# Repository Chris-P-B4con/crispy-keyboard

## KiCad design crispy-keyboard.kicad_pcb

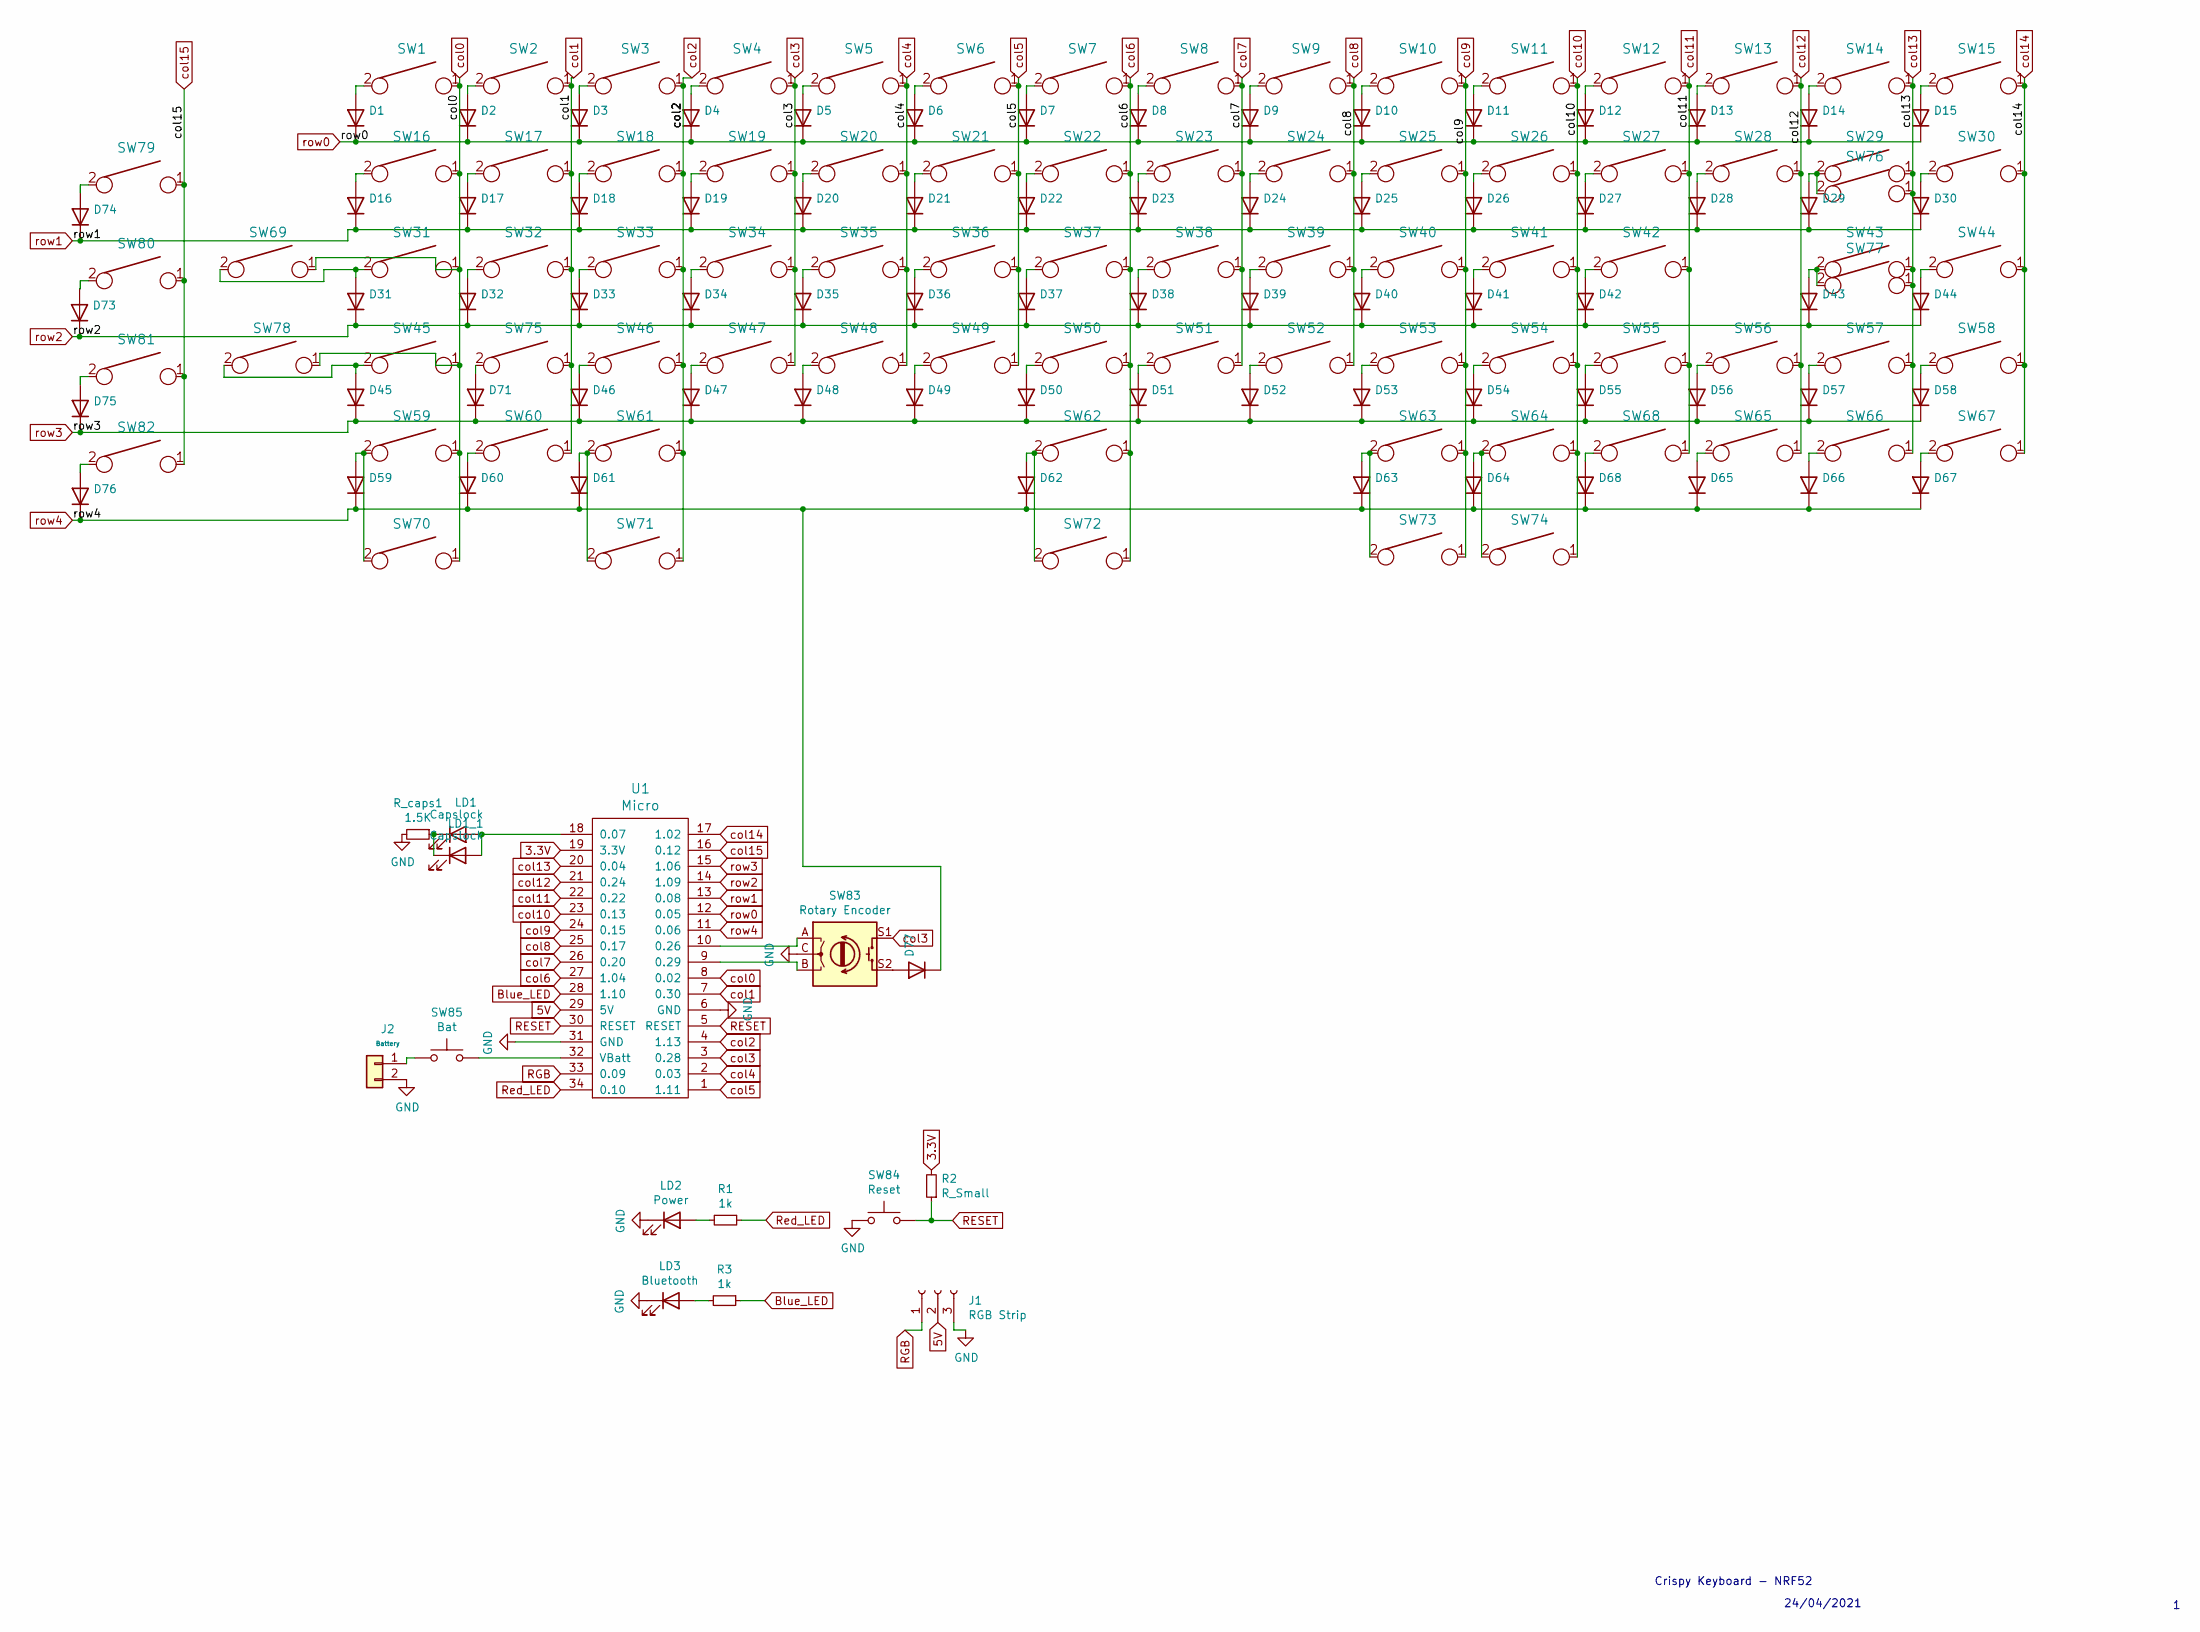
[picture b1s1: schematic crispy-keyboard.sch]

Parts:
D1, D2, D3, D4, D5, D6, D7, D8, D9, D10, D11, D12, D13, D14, D15, D16, D17, D18, D19, D20, D21, D22, D23, D24, D25, D26, D27, D28, D29, D30, D31, D32, D33, D34, D35, D36, D37, D38, D39, D40, D41, D42, D43, D44, D45, D46, D47, D48, D49, D50, D51, D52, D53, D54, D55, D56, D57, D58, D59, D60, D61, D62, D63, D64, D65, D66, D67, D68, D71, D73, D74, D75, D76, D77: D_DO-35_SOD27_P5.08mm_Horizontal
J1: RGB Strip; PinHeader_1x03_P2.00mm_Horizontal
J2: Battery; PinHeader_1x02_P2.54mm_Vertical
LD1, LD1_1: Capslock; LED_D3.0mm
LD2: Power; LED_D3.0mm
LD3: Bluetooth; LED_D3.0mm
R1, R3: 1k; R_Axial_DIN0204_L3.6mm_D1.6mm_P5.08mm_Horizontal
R2: R_Small; R_Axial_DIN0204_L3.6mm_D1.6mm_P5.08mm_Horizontal
R_caps1: 1.5K; R_Axial_DIN0204_L3.6mm_D1.6mm_P5.08mm_Horizontal
SW1, SW2, SW3, SW4, SW5, SW6, SW7, SW8, SW9, SW10, SW11, SW12, SW13, SW15, SW17, SW18, SW19, SW20, SW21, SW22, SW23, SW24, SW25, SW26, SW27, SW28, SW30, SW32, SW33, SW34, SW35, SW36, SW37, SW38, SW39, SW40, SW41, SW42, SW44, SW46, SW47, SW48, SW49, SW50, SW51, SW52, SW53, SW54, SW55, SW57, SW58, SW62, SW65, SW66, SW67, SW68, SW72, SW75, SW77, SW79, SW80, SW81, SW82: KEYSW; SW_Cherry_MX1A_1.00u_PCB-NOSCREEN
SW14: KEYSW; SW_Cherry_MX1A_2.00u_PCBNOSCREEN
SW16, SW29, SW70, SW71, SW73, SW74: KEYSW; SW_Cherry_MX1A_1.50u_PCBNOSCREEN
SW31, SW56: KEYSW; SW_Cherry_MX1A_1.75u_PCBNOSCREEN
SW43, SW45: KEYSW; SW_Cherry_MX1A_2.25u_PCBNOSCREEN
SW59, SW60, SW61, SW63, SW64, SW69, SW78: KEYSW; SW_Cherry_MX1A_1.25u_PCBNOSCREEN
SW76: KEYSW; SW_Cherry_MX1A_ISOEnter_PCB_ReversedStabilizer
SW83: Rotary Encoder; Bourns-PEC11R-4120F-S0018-MFG
SW84: Reset; SW_PUSH_6mm
SW85: Bat; CK_Switches-L101011ML04Q-0-0-MFG
U1: Micro; arduino_micro_large

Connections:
3.3V: R2.2, U1.19 (3.3V)
5V: J1.2, U1.29 (5V)
Blue_LED: R3.1, U1.28 (1.10)
GND: J1.3, J2.2, LD2.1 (K), LD3.1 (K), R_caps1.2, SW83.C, SW84.2, U1.6 (GND), U1.31 (GND); also elsewhere on the board
unnamed: D1.2 (A), SW1.2
unnamed: D2.2 (A), SW2.2
unnamed: D3.2 (A), SW3.2
unnamed: D4.2 (A), SW4.2
unnamed: D5.2 (A), SW5.2
unnamed: D6.2 (A), SW6.2
unnamed: D7.2 (A), SW7.2
unnamed: D8.2 (A), SW8.2
unnamed: D9.2 (A), SW9.2
unnamed: D10.2 (A), SW10.2
unnamed: D11.2 (A), SW11.2
unnamed: D12.2 (A), SW12.2
unnamed: D13.2 (A), SW13.2
unnamed: D14.2 (A), SW14.2
unnamed: D15.2 (A), SW15.2
unnamed: D16.2 (A), SW16.2
unnamed: D17.2 (A), SW17.2
unnamed: D18.2 (A), SW18.2
unnamed: D19.2 (A), SW19.2
unnamed: D20.2 (A), SW20.2
unnamed: D21.2 (A), SW21.2
unnamed: D22.2 (A), SW22.2
unnamed: D23.2 (A), SW23.2
unnamed: D24.2 (A), SW24.2
unnamed: D25.2 (A), SW25.2
unnamed: D26.2 (A), SW26.2
unnamed: D27.2 (A), SW27.2
unnamed: D28.2 (A), SW28.2
unnamed: D29.2 (A), SW29.2, SW76.2
unnamed: D30.2 (A), SW30.2
unnamed: D31.2 (A), SW31.2, SW69.2
unnamed: D32.2 (A), SW32.2
unnamed: D33.2 (A), SW33.2
unnamed: D34.2 (A), SW34.2
unnamed: D35.2 (A), SW35.2
unnamed: D36.2 (A), SW36.2
unnamed: D37.2 (A), SW37.2
unnamed: D38.2 (A), SW38.2
unnamed: D39.2 (A), SW39.2
unnamed: D40.2 (A), SW40.2
unnamed: D41.2 (A), SW41.2
unnamed: D42.2 (A), SW42.2
unnamed: D43.2 (A), SW43.2, SW77.2
unnamed: D44.2 (A), SW44.2
unnamed: D45.2 (A), SW45.2, SW78.2
unnamed: D46.2 (A), SW46.2
unnamed: D47.2 (A), SW47.2
unnamed: D48.2 (A), SW48.2
unnamed: D49.2 (A), SW49.2
unnamed: D50.2 (A), SW50.2
unnamed: D51.2 (A), SW51.2
unnamed: D52.2 (A), SW52.2
unnamed: D53.2 (A), SW53.2
unnamed: D54.2 (A), SW54.2
unnamed: D55.2 (A), SW55.2
unnamed: D56.2 (A), SW56.2
unnamed: D57.2 (A), SW57.2
unnamed: D58.2 (A), SW58.2
unnamed: D59.2 (A), SW59.2, SW70.2
unnamed: D60.2 (A), SW60.2
unnamed: D61.2 (A), SW61.2, SW71.2
unnamed: D62.2 (A), SW62.2, SW72.2
unnamed: D63.2 (A), SW63.2, SW73.2
unnamed: D64.2 (A), SW64.2, SW74.2
unnamed: D65.2 (A), SW65.2
unnamed: D66.2 (A), SW66.2
unnamed: D67.2 (A), SW67.2
unnamed: D68.2 (A), SW68.2
unnamed: D71.2 (A), SW75.2
unnamed: D73.2 (A), SW80.2
unnamed: D74.2 (A), SW79.2
unnamed: D75.2 (A), SW81.2
unnamed: D76.2 (A), SW82.2
unnamed: D77.2 (A), SW83.S2
unnamed: J2.1, SW85.2
unnamed: LD1.1 (K), LD1_1.1 (K), R_caps1.1
unnamed: LD1.2 (A), LD1_1.2 (A), U1.18 (0.07)
unnamed 81: LD2.2 (A), R1.2; also elsewhere on the board
unnamed 82: LD3.2 (A), R3.2; also elsewhere on the board
unnamed: SW83.A, U1.10 (0.26)
unnamed: SW83.B, U1.9 (0.29)
unnamed: SW85.1, U1.32 (VBatt)
RESET: R2.1, SW84.1, U1.5 (RESET), U1.30 (RESET)
RGB: J1.1, U1.33 (0.09)
Red_LED: R1.1, U1.34 (0.10)
col0: SW1.1, SW16.1, SW31.1, SW45.1, SW59.1, SW69.1, SW70.1, SW78.1, U1.8 (0.02)
col1: SW2.1, SW17.1, SW32.1, SW60.1, SW75.1, U1.7 (0.30)
col2: SW3.1, SW18.1, SW33.1, SW46.1, SW61.1, SW71.1, U1.4 (1.13)
col3: SW4.1, SW19.1, SW34.1, SW47.1, SW83.S1, U1.3 (0.28)
col4: SW5.1, SW20.1, SW35.1, SW48.1, U1.2 (0.03)
col5: SW6.1, SW21.1, SW36.1, SW49.1, U1.1 (1.11)
col6: SW7.1, SW22.1, SW37.1, SW50.1, SW62.1, SW72.1, U1.27 (1.04)
col7: SW8.1, SW23.1, SW38.1, SW51.1, U1.26 (0.20)
col8: SW9.1, SW24.1, SW39.1, SW52.1, U1.25 (0.17)
col9: SW10.1, SW25.1, SW40.1, SW53.1, SW63.1, SW73.1, U1.24 (0.15)
col10: SW11.1, SW26.1, SW41.1, SW54.1, SW64.1, SW74.1, U1.23 (0.13)
col11: SW12.1, SW27.1, SW42.1, SW55.1, SW68.1, U1.22 (0.22)
col12: SW13.1, SW28.1, SW56.1, SW65.1, U1.21 (0.24)
col13: SW14.1, SW29.1, SW43.1, SW57.1, SW66.1, SW76.1, SW77.1, U1.20 (0.04)
col14: SW15.1, SW30.1, SW44.1, SW58.1, SW67.1, U1.17 (1.02)
col15: SW79.1, SW80.1, SW81.1, SW82.1, U1.16 (0.12)
row0: D1.1 (K), D2.1 (K), D3.1 (K), D4.1 (K), D5.1 (K), D6.1 (K), D7.1 (K), D8.1 (K), D9.1 (K), D10.1 (K), D11.1 (K), D12.1 (K), D13.1 (K), D14.1 (K), D15.1 (K), U1.12 (0.05)
row1: D16.1 (K), D17.1 (K), D18.1 (K), D19.1 (K), D20.1 (K), D21.1 (K), D22.1 (K), D23.1 (K), D24.1 (K), D25.1 (K), D26.1 (K), D27.1 (K), D28.1 (K), D29.1 (K), D30.1 (K), D74.1 (K), U1.13 (0.08)
row2: D31.1 (K), D32.1 (K), D33.1 (K), D34.1 (K), D35.1 (K), D36.1 (K), D37.1 (K), D38.1 (K), D39.1 (K), D40.1 (K), D41.1 (K), D42.1 (K), D43.1 (K), D44.1 (K), D73.1 (K), U1.14 (1.09)
row3: D45.1 (K), D46.1 (K), D47.1 (K), D48.1 (K), D49.1 (K), D50.1 (K), D51.1 (K), D52.1 (K), D53.1 (K), D54.1 (K), D55.1 (K), D56.1 (K), D57.1 (K), D58.1 (K), D71.1 (K), D75.1 (K), U1.15 (1.06)
row4: D59.1 (K), D60.1 (K), D61.1 (K), D62.1 (K), D63.1 (K), D64.1 (K), D65.1 (K), D66.1 (K), D67.1 (K), D68.1 (K), D76.1 (K), D77.1 (K), U1.11 (0.06)

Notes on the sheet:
24/04/2021
Crispy Keyboard - NRF52

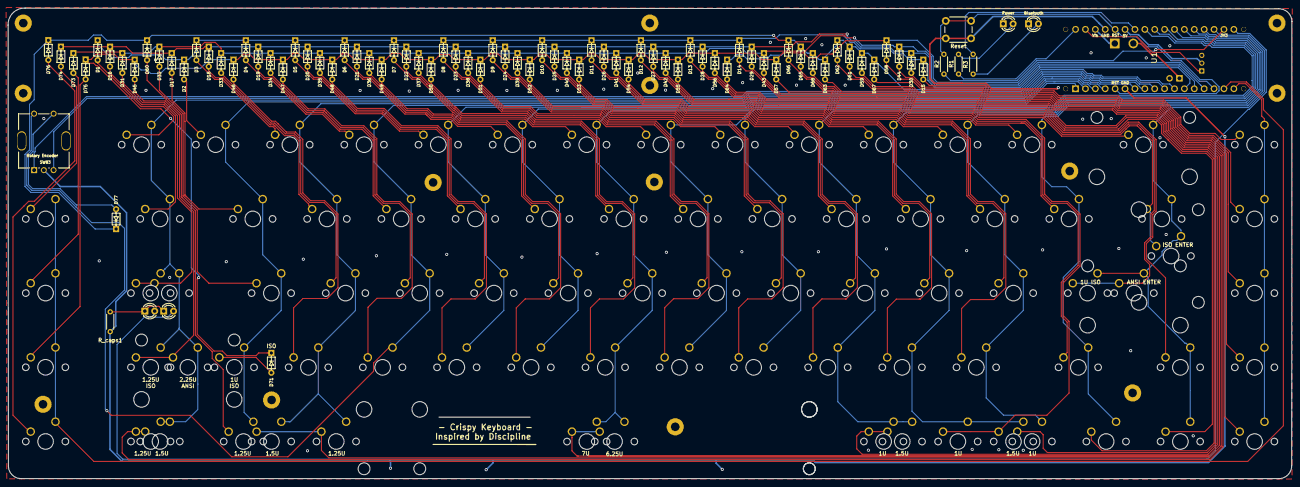
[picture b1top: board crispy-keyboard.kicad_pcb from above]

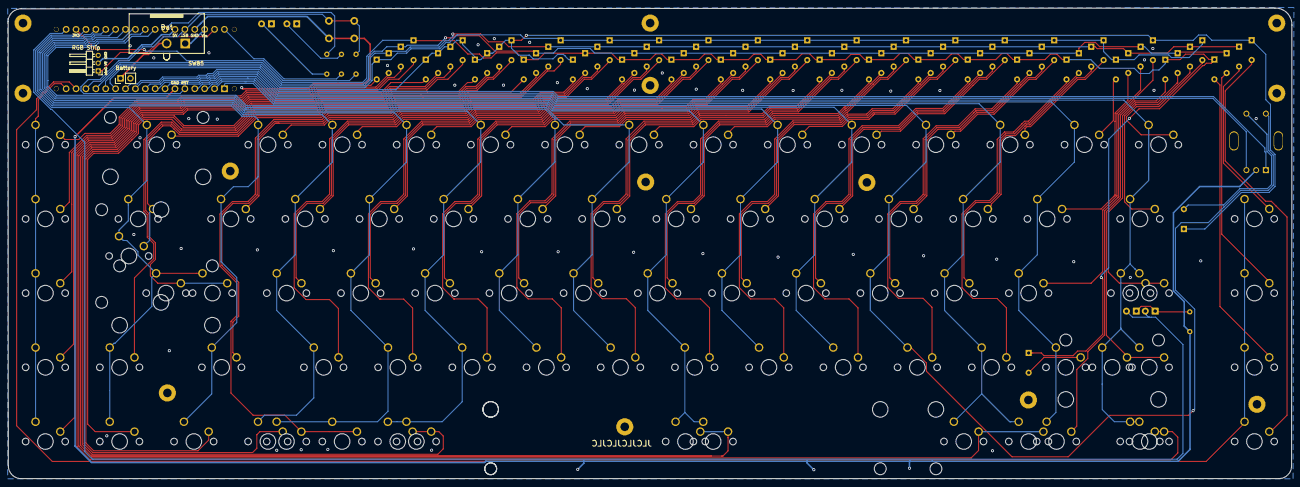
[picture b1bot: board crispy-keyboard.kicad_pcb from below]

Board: 2 copper layers, 329.6 x 120.8 mm, 171 parts (3 on the bottom side), 110 nets.

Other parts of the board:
Bluetooth: Bluetooth; LED_D3.0mm
Power: Power; LED_D3.0mm
ST62: 7U; MX-7U-Stabilizer

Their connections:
GND: Bluetooth.1, Power.1; also elsewhere on the board
unnamed 81: Power.2; also elsewhere on the board
unnamed 82: Bluetooth.2; also elsewhere on the board

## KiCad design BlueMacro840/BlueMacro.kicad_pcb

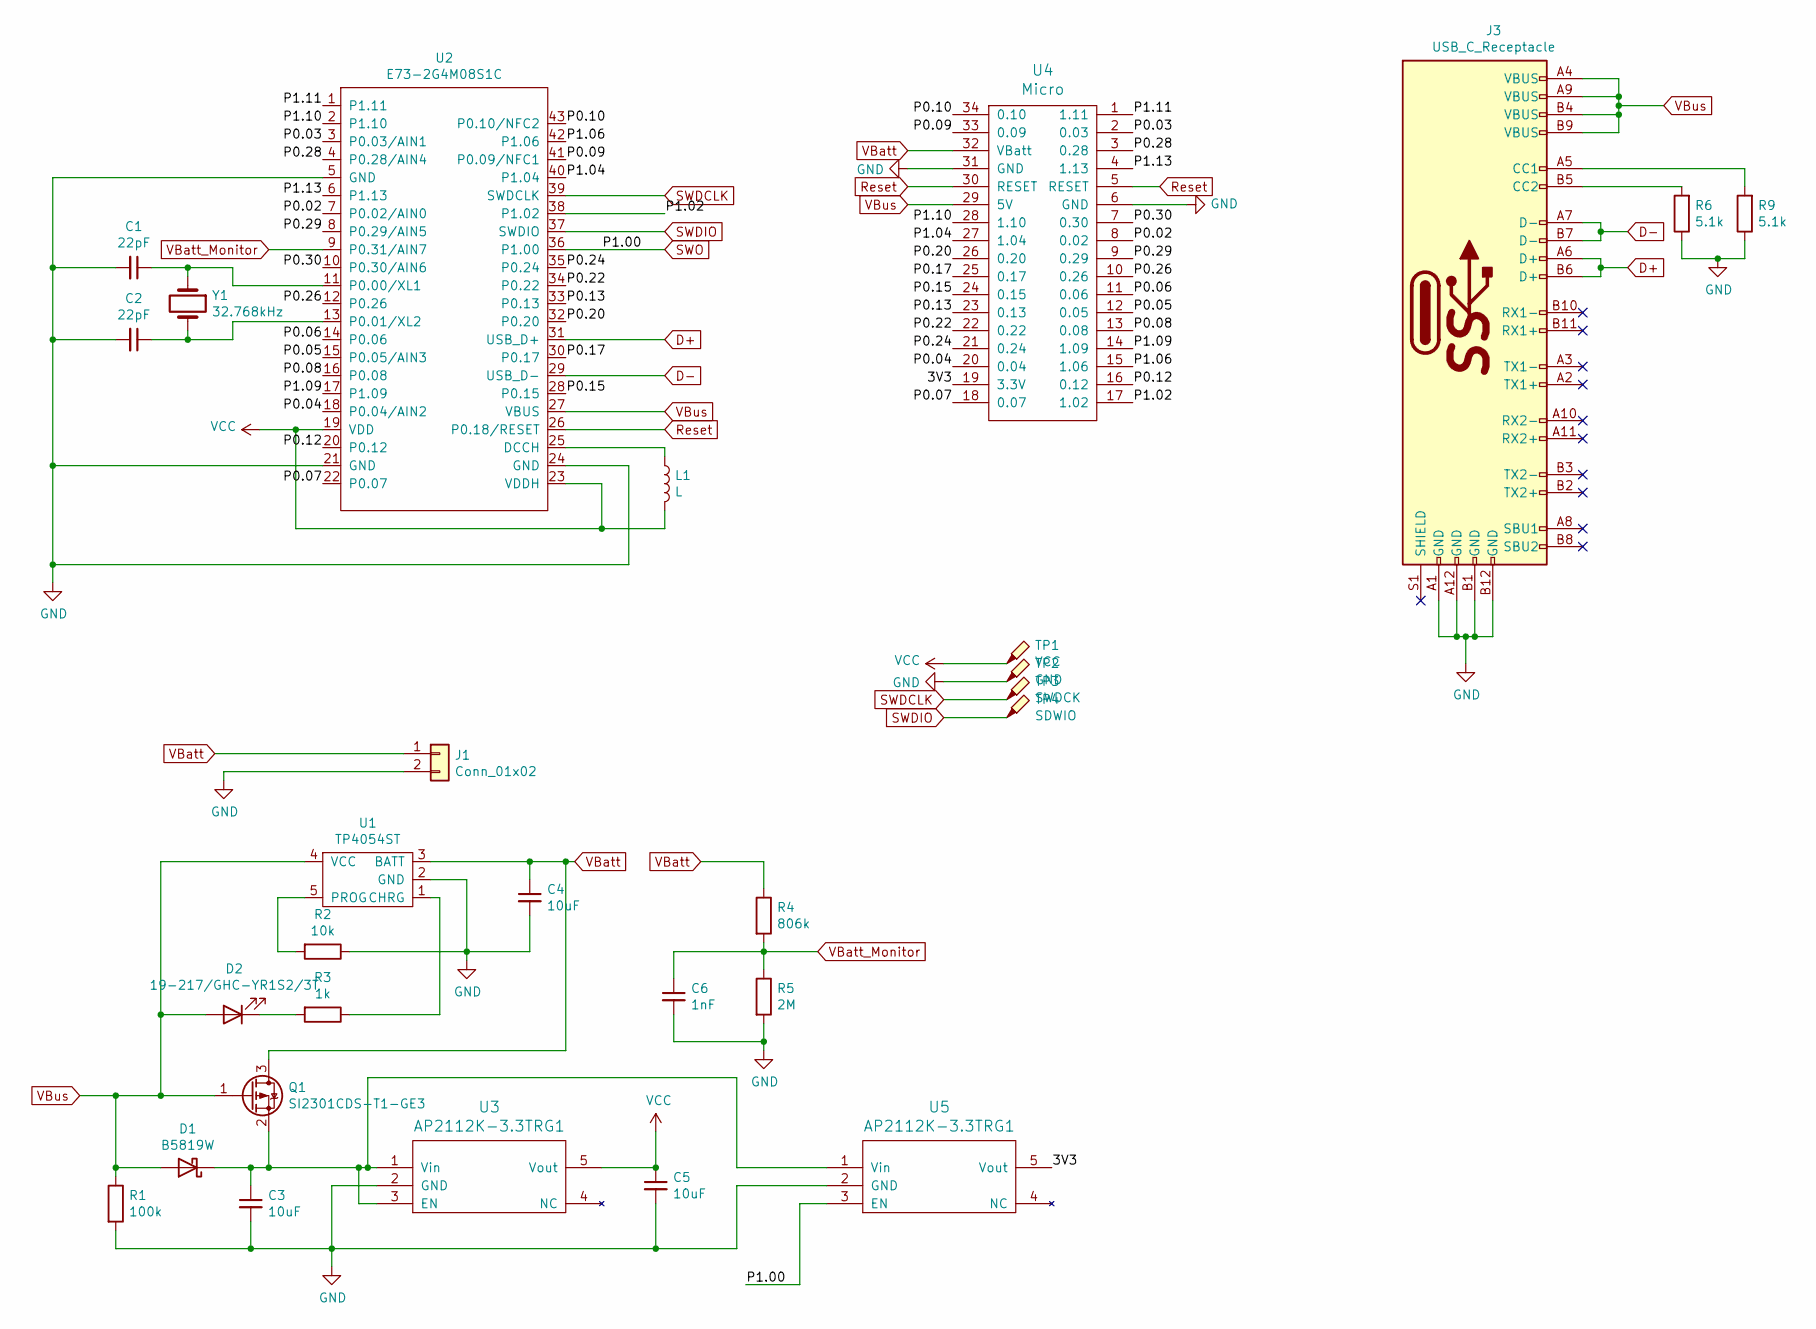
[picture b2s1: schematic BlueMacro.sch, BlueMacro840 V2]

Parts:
C1, C2: 22pF; C_0603_1608Metric; LCSC C1653
C3, C4, C5: 10uF; C_0603_1608Metric; LCSC C19702
C6: 1nF; C_0603_1608Metric; LCSC C1588
D1: B5819W; D_SOD-123; LCSC C8598
D2: 19-217/GHC-YR1S2/3T; LED_0603_1608Metric; LCSC C72043
J1: Conn_01x02; PinHeader_1x02_P2.54mm_Vertical
J3: USB_C_Receptacle; HRO-TYPE-C-31-M-12-C165948; LCSC C165948
L1: L; L_0805_2012Metric; LCSC C1046
Q1: SI2301CDS-T1-GE3; SOT-23; LCSC C10487
R1: 100k; R_0603_1608Metric; LCSC C25803
R2: 10k; R_0603_1608Metric; LCSC C25804
R3: 1k; R_0603_1608Metric; LCSC C21190
R4: 806k; R_0603_1608Metric; LCSC C23250
R5: 2M; R_0603_1608Metric; LCSC C22976
R6, R9: 5.1k; R_0603_1608Metric; LCSC C23186
TP1: VCC; TestPoint_THTPad_1.1x1.1mm_Drill0.8mm
TP2: GND; TestPoint_THTPad_1.1x1.1mm_Drill0.8mm
TP3: SWDCK; TestPoint_THTPad_1.1x1.1mm_Drill0.8mm
TP4: SDWIO; TestPoint_THTPad_1.1x1.1mm_Drill0.8mm
U1: TP4054ST; SOT-23-5; LCSC C32574
U2: E73-2G4M08S1C; E73-2G4M08S1C-52840
U3, U5: AP2112K-3.3TRG1; SOT-23-5; LCSC C51118
U4: Micro; arduino_micro
Y1: 32.768kHz; Crystal_SMD_3215-2Pin_3.2x1.5mm; LCSC C32346

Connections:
/3V3: U4.19 (3.3V), U5.5 (Vout)
/P0.02: U2.7 (P0.02/AIN0), U4.8 (0.02)
/P0.03: U2.3 (P0.03/AIN1), U4.2 (0.03)
/P0.04: U2.18 (P0.04/AIN2), U4.20 (0.04)
/P0.05: U2.15 (P0.05/AIN3), U4.12 (0.05)
/P0.06: U2.14 (P0.06), U4.11 (0.06)
/P0.07: U2.22 (P0.07), U4.18 (0.07)
/P0.08: U2.16 (P0.08), U4.13 (0.08)
/P0.09: U2.41 (P0.09/NFC1), U4.33 (0.09)
/P0.10: U2.43 (P0.10/NFC2), U4.34 (0.10)
/P0.12: U2.20 (P0.12), U4.16 (0.12)
/P0.13: U2.33 (P0.13), U4.23 (0.13)
/P0.15: U2.28 (P0.15), U4.24 (0.15)
/P0.17: U2.30 (P0.17), U4.25 (0.17)
/P0.20: U2.32 (P0.20), U4.26 (0.20)
/P0.22: U2.34 (P0.22), U4.22 (0.22)
/P0.24: U2.35 (P0.24), U4.21 (0.24)
/P0.26: U2.12 (P0.26), U4.10 (0.26)
/P0.28: U2.4 (P0.28/AIN4), U4.3 (0.28)
/P0.29: U2.8 (P0.29/AIN5), U4.9 (0.29)
/P0.30: U2.10 (P0.30/AIN6), U4.7 (0.30)
/P1.02: U2.38 (P1.02), U4.17 (1.02)
/P1.04: U2.40 (P1.04), U4.27 (1.04)
/P1.06: U2.42 (P1.06), U4.15 (1.06)
/P1.09: U2.17 (P1.09), U4.14 (1.09)
/P1.10: U2.2 (P1.10), U4.28 (1.10)
/P1.11: U2.1 (P1.11), U4.1 (1.11)
/P1.13: U2.6 (P1.13), U4.4 (1.13)
D+: J3.A6 (D+), J3.B6 (D+), U2.31 (USB_D+)
D-: J3.A7 (D-), J3.B7 (D-), U2.29 (USB_D-)
GND: C1.2, C2.2, C3.2, C4.2, C5.2, C6.2, J1.2, J3.A1 (GND), J3.A12 (GND), J3.B1 (GND), J3.B12 (GND), R1.2, R2.1, R5.2, R6.1, R9.1, TP2.1, U1.2 (GND), U2.5 (GND), U2.21 (GND), U2.24 (GND), U3.2 (GND), U4.6 (GND), U4.31 (GND), U5.2 (GND)
unnamed: C1.1, U2.11 (P0.00/XL1), Y1.1
unnamed: C2.1, U2.13 (P0.01/XL2), Y1.2
unnamed: C3.1, D1.1 (K), Q1.2 (S), U3.1 (Vin), U3.3 (EN), U5.1 (Vin)
unnamed: D2.1 (K), R3.2
unnamed: J3.A5 (CC1), R9.2
unnamed: J3.B5 (CC2), R6.2
unnamed: L1.1, U2.25 (DCCH)
unnamed: R2.2, U1.5 (PROG)
unnamed: R3.1, U1.1 (CHRG)
Reset: U2.26 (P0.18/RESET), U4.5 (RESET), U4.30 (RESET)
SWDCLK: TP3.1, U2.39 (SWDCLK)
SWDIO: TP4.1, U2.37 (SWDIO)
SWO: U2.36 (P1.00), U5.3 (EN)
VBatt: C4.1, J1.1, Q1.3 (D), R4.1, U1.3 (BATT), U4.32 (VBatt)
VBatt_Monitor: C6.1, R4.2, R5.1, U2.9 (P0.31/AIN7)
VBus: D1.2 (A), D2.2 (A), J3.A4 (VBUS), J3.A9 (VBUS), J3.B4 (VBUS), J3.B9 (VBUS), Q1.1 (G), R1.1, U1.4 (VCC), U2.27 (VBUS), U4.29 (5V)
VCC: C5.1, L1.2, TP1.1, U2.19 (VDD), U2.23 (VDDH), U3.5 (Vout)

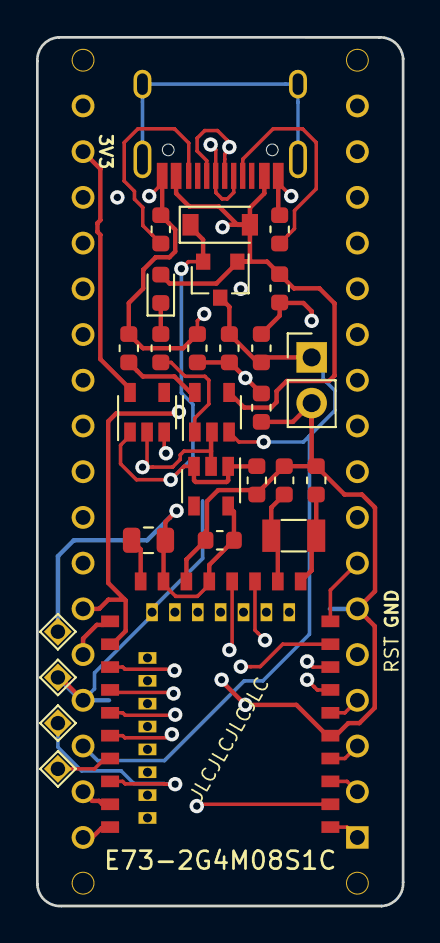
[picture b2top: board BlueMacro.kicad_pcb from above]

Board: 4 copper layers, 20.3 x 48.3 mm, 29 parts (0 on the bottom side), 48 nets.

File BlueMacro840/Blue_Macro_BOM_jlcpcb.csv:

Comment;Designator;Footprint;LCSC Part Number
22pF;C1,C2;Capacitor_SMD:C_0603_1608Metric;C1653
10uF;C3,C4,C5;Capacitor_SMD:C_0603_1608Metric;C19702
1nF;C6;Capacitor_SMD:C_0603_1608Metric;C1588
B5819W;D1;Diode_SMD:D_SOD-123;C8598
19-217/GHC-YR1S2/3T;D2;LED_SMD:LED_0603_1608Metric;C72043
USB_C_Receptacle;J3;footprints:HRO-TYPE-C-31-M-12-C165948;C165948
L;L1;Inductor_SMD:L_0805_2012Metric;C1046
SI2301CDS-T1-GE3;Q1;Package_TO_SOT_SMD:SOT-23;C10487
100k;R1;Resistor_SMD:R_0603_1608Metric;C25803
10k;R2;Resistor_SMD:R_0603_1608Metric;C25804
1k;R3;Resistor_SMD:R_0603_1608Metric;C21190
806k;R4;Resistor_SMD:R_0603_1608Metric;C23250
2M;R5;Resistor_SMD:R_0603_1608Metric;C22976
5.1k;R6,R9;Resistor_SMD:R_0603_1608Metric;C23186
TP4054ST;U1;Package_TO_SOT_SMD:SOT-23-5;C32574
E73-2G4M08S1C;U2;E73:E73-2G4M08S1C-52840;C356849
AP2112K-3.3TRG1;U3,U5;Package_TO_SOT_SMD:SOT-23-5;C51118
32.768kHz;Y1;Crystal:Crystal_SMD_3215-2Pin_3.2x1.5mm;C32346

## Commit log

2020-12-01 Corrected mistakes (wildkeeb.txt), added pins for RGB underglow and battery
2020-12-01 Changed power pin of external RGB LED Strip to POW_5V from USB_POW
2020-12-04 Connected both USB D+ D-
2020-12-06 Added PCB edges, swapped USB-C footprint
2021-04-26 Changed board to BlueMacro. Switched rotary encoder
2021-04-27 Shifted macro footprint for better usb access. Shifted rotary encoder footprint for better access
2021-05-04 Added BlueMacro PCB. Added Plate PCB.
2021-05-06 Finished plate
2021-06-14 Finished Plate. Fixed errors (missing via, missing solder mask) on BlueMacro
